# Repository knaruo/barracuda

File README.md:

# barracuda
barracuda (Thin Plate Keyboard)

**PCB (kicad 3D viewer)**

# Concept

* Ortholinear
  * 3 rows \* 6 columns on left, 5 columns on right, total 33 keys
* Key switch hot-swap capable
  * Supports Kailh PCB socket for Kailh Choc V1 low profile switches
* Very thin design
  * Only supports SMT diodes (1N4148W)
  * Not using ProMicro but using ATmega32U2 mounted directly on PCB.
* Dimension
  * Length: 271.4 mm
  * Width: 59.7 mm
  * Height (PCB bottom to key top): About 15 mm
    * NOTE: with Kailh Choc (V1) switch and Kailh key caps.

# BOM list

| Name                | Parts id          | Number |
| ------------------- | ----------------- | ------ |
| MCU                 | ATmega32U2 (TQFP) | 1      |
| Socket (ChocV1)     | CPG135001S30      | 33     |
| Diode               | 1N4148W           | 33     |
| Reset Switch        | TVAF06-A020B-R    | 1      |
| Spacer (M2 4mm)     | ARB-2004E         | 10     |
| Thread (M2 3mm)     | -                 | 20     |
| USB micro connector | -                 | 1      |
| Poly fuse           | -                 | 1      |
| Crystal (16MHz)     | FA238             | 1      |
| Resistor (22ohm)    | 2012size          | 2      |
| Resistor (10kohm)   | 2012size          | 2      |
| Capacitor (22pF)    | 1608size          | 2      |
| Capacitor (0.1uF)   | 1608size          | 2      |
| Capacitor (1uF)     | 1608size          | 1      |
| Capacitor (10uF)    | 2012size          | 1      |

# Firmware

QMK support is available in my forked [qmk_firmware](https://github.com/knaruo/qmk_firmware) (barracuda/default)

# Build Guide

[ビルドガイド](doc/build_guide_ja.md)

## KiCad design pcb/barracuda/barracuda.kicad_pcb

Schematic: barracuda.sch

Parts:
C1, C2: 22p; C_0603_1608Metric_Pad1.08x0.95mm_HandSolder
C3, C6: 0.1u; C_0603_1608Metric_Pad1.08x0.95mm_HandSolder
C4: 10u; C_0805_2012Metric_Pad1.18x1.45mm_HandSolder
C5: 1u; C_0603_1608Metric_Pad1.08x0.95mm_HandSolder
D1, D2, D3, D4, D5, D6, D7, D8, D9, D10, D11, D12, D13, D14, D15, D16, D17, D18, D19, D20, D21, D22, D23, D24, D25, D26, D27, D28, D29, D30, D31, D32, D33: D; D3_SMD
F1: Polyfuse_Small; RESC1206X70N
J1: USB_B_Micro; HRS_ZX62R-B-5P
R1, R2: 22; R_0805_2012Metric_Pad1.20x1.40mm_HandSolder
R3, R4: 10k; R_0805_2012Metric_Pad1.20x1.40mm_HandSolder
RSTSW1: SW_PUSH; TVAF06-A020B-R
SW1, SW2, SW3, SW4, SW5, SW6, SW7, SW8, SW9, SW10, SW11, SW12, SW13, SW14, SW15, SW16, SW17, SW18, SW19, SW20, SW21, SW22, SW23, SW24, SW25, SW26, SW27, SW28, SW29, SW30, SW31, SW32, SW33: SW_PUSH; ChocV1_V2_Hotswap
U1: ATmega32U2-AU; TQFP-32_7x7mm_P0.8mm
Y1: Crystal_GND24_Small; Crystal_SMD_SeikoEpson_FA238-4Pin_3.2x2.5mm_HandSoldering

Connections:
GND: C1.2, C2.2, C3.2, C4.2, C5.2, C6.2, J1.5, J1.6, R4.2, RSTSW1.1, U1.3, U1.28, Y1.2, Y1.4
unnamed: C1.1, U1.1, Y1.1
unnamed: C2.1, U1.2, Y1.3
unnamed: C3.1, U1.27
unnamed: D1.2 (A), SW1.2
unnamed: D2.2 (A), SW2.2
unnamed: D3.2 (A), SW3.2
unnamed: D4.2 (A), SW4.2
unnamed: D5.2 (A), SW5.2
unnamed: D6.2 (A), SW6.2
unnamed: D7.2 (A), SW7.2
unnamed: D8.2 (A), SW8.2
unnamed: D9.2 (A), SW9.2
unnamed: D10.2 (A), SW10.2
unnamed: D11.2 (A), SW11.2
unnamed: D12.2 (A), SW12.2
unnamed: D13.2 (A), SW13.2
unnamed: D14.2 (A), SW14.2
unnamed: D15.2 (A), SW15.2
unnamed: D16.2 (A), SW16.2
unnamed: D17.2 (A), SW17.2
unnamed: D18.2 (A), SW18.2
unnamed: D19.2 (A), SW19.2
unnamed: D20.2 (A), SW20.2
unnamed: D21.2 (A), SW21.2
unnamed: D22.2 (A), SW22.2
unnamed: D23.2 (A), SW23.2
unnamed: D24.2 (A), SW24.2
unnamed: D25.2 (A), SW25.2
unnamed: D26.2 (A), SW26.2
unnamed: D27.2 (A), SW27.2
unnamed: D28.2 (A), SW28.2
unnamed: D29.2 (A), SW29.2
unnamed: D30.2 (A), SW30.2
unnamed: D31.2 (A), SW31.2
unnamed: D32.2 (A), SW32.2
unnamed: D33.2 (A), SW33.2
unnamed: F1.2, J1.1
unnamed: J1.2, R2.2
unnamed: J1.3, R1.2
unnamed: R4.1, U1.13
VCC: C4.1, C5.1, C6.1, F1.1, R3.1, U1.4, U1.31, U1.32
col0: SW1.1, SW2.1, SW3.1, U1.10
col1: SW4.1, SW5.1, SW6.1, SW19.1, SW20.1, SW21.1, U1.11
col2: SW7.1, SW8.1, SW9.1, SW22.1, SW23.1, SW24.1, U1.12
col3: SW10.1, SW11.1, SW12.1, SW25.1, SW26.1, SW27.1, U1.14
col4: SW13.1, SW14.1, SW15.1, SW28.1, SW29.1, SW30.1, U1.15
col5: SW16.1, SW17.1, SW18.1, SW31.1, SW32.1, SW33.1, U1.16
d_m: R2.1, U1.30
d_p: R1.1, U1.29
reset: R3.2, RSTSW1.2, U1.24
row0: D1.1 (K), D4.1 (K), D7.1 (K), D10.1 (K), D13.1 (K), D16.1 (K), U1.26
row1: D2.1 (K), D5.1 (K), D8.1 (K), D11.1 (K), D14.1 (K), D17.1 (K), U1.25
row2: D3.1 (K), D6.1 (K), D9.1 (K), D12.1 (K), D15.1 (K), D18.1 (K), U1.23
row3: D19.1 (K), D22.1 (K), D25.1 (K), D28.1 (K), D31.1 (K), U1.7
row4: D20.1 (K), D23.1 (K), D26.1 (K), D29.1 (K), D32.1 (K), U1.8
row5: D21.1 (K), D24.1 (K), D27.1 (K), D30.1 (K), D33.1 (K), U1.9

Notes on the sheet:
Power Flags
Reset Circuit
Pro Micro
Switch Matrix

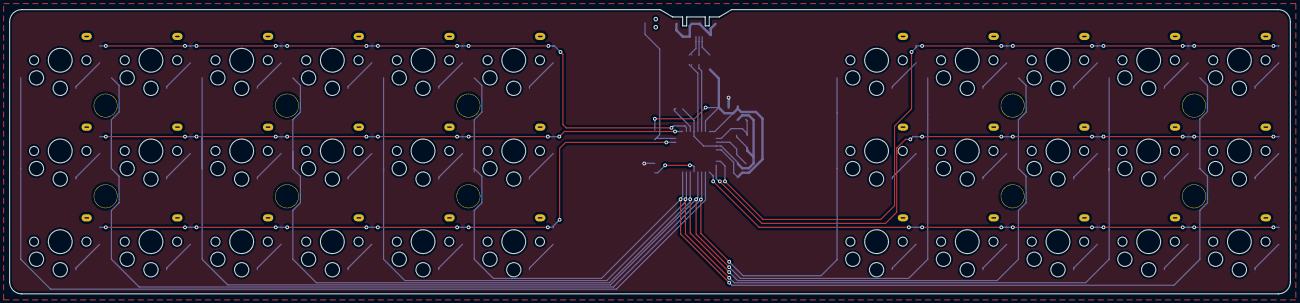
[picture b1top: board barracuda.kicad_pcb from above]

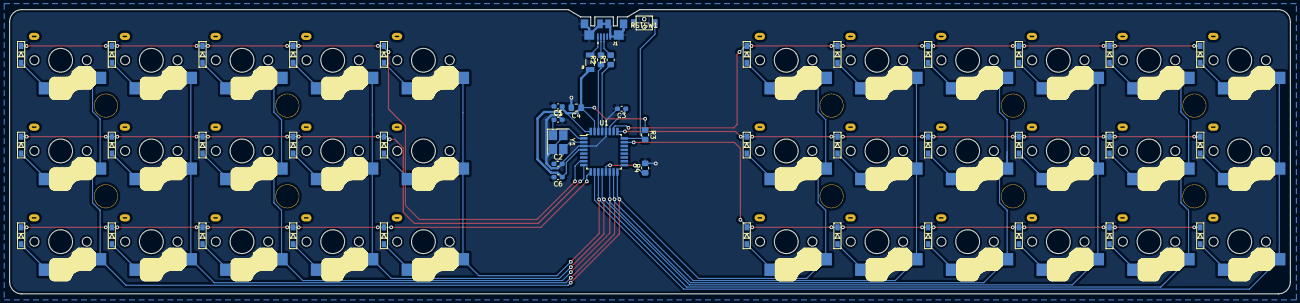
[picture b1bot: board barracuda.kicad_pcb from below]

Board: 2 copper layers, 268.9 x 59.6 mm, 91 parts (15 on the bottom side), 57 nets.

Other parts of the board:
HOLE1, HOLE2, HOLE7, HOLE8, HOLE13, HOLE14, HOLE22, HOLE23, HOLE28, HOLE29: HOLE

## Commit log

2020-11-09 Added files from Keyboard Layout Editor
2020-11-09 Added files from Keyboard Layout Editor (#2)
2020-11-09 Added Plate & Case Builder file for the top plate (No thread holes)
2020-11-09 Added Plate & Case Builder file for the top plate (No thread holes) (#4)
2020-11-15 Created the circuit diagram
2020-11-15 Created the circuit diagram (#6)
2020-12-27 Reduced to 33 keys
2020-12-27 Assigned footprint to each components
2020-12-27 Generated PCB from net list
2020-12-27 Determined keyswitch layout and footprint
2020-12-27 Located mounting holes
2020-12-27 Located diodes (NOTE: some diodes conflict with mounting holes)
2020-12-27 Resolved conflict of mounting holes and some diodes
2020-12-27 Rough sketch of Edge.cuts
2020-12-27 Created vias for all diodes
2020-12-27 Connected obvious tracks
2020-12-28 Reassigned col/rows
2020-12-28 Connected trivial tracks
2020-12-28 Connected each columns
2020-12-28 connected rows
2021-01-01 PCB almost done
2021-01-01 Replaced KeySwitch and diode footprints
2021-01-02 Connected most of rows/columns
2021-01-03 Updated the MCU to atmega32u2
2021-01-09 save
2021-01-09 Finished routing
2021-01-09 Finalized routing
2021-01-09 Done with bottom plate
2021-01-09 Done with the top plate
2021-01-09 Added credit
2021-01-09 Generated gerber files
2021-01-09 Regenerated gerber files to avoid errors in JLCPCB
2021-01-09 Issue8 barracuda lp (#9)
    * Reduced to 33 keys
    * Assigned footprint to each components
    * Generated PCB from net list
    * Determined keyswitch layout and footprint
    * Located mounting holes
    * Located diodes (NOTE: some diodes conflict with mounting holes)
2021-01-23 Added README.md with built keyboard picture
2021-01-23 Added README.md with built keyboard picture (#11)
2021-01-23 Create LICENSE
2021-01-23 Create LICENSE (#12)
2021-02-13 Added Dimension data in README.md
2021-02-13 Added Dimension data in README.md (#14)
2021-02-14 Build Guide (Ja) draft
2021-02-20 update build guide
2021-02-20 Updated build guide
2021-02-20 Added pictures on build guide
2021-02-20 png -> PNG
2021-02-27 almost done with the build guide
2021-02-27 How to build (#16)
    * Build Guide (Ja) draft
    * update build guide
    * Updated build guide
    * Added pictures on build guide
    * png -> PNG
    * Updated build guide
2021-02-27 Added firmware information
2021-02-27 Added firmware information (#18)
2021-05-22 Updated build_guide
2021-05-22 Updated build_guide (#20)
2021-05-23 Minor fix
